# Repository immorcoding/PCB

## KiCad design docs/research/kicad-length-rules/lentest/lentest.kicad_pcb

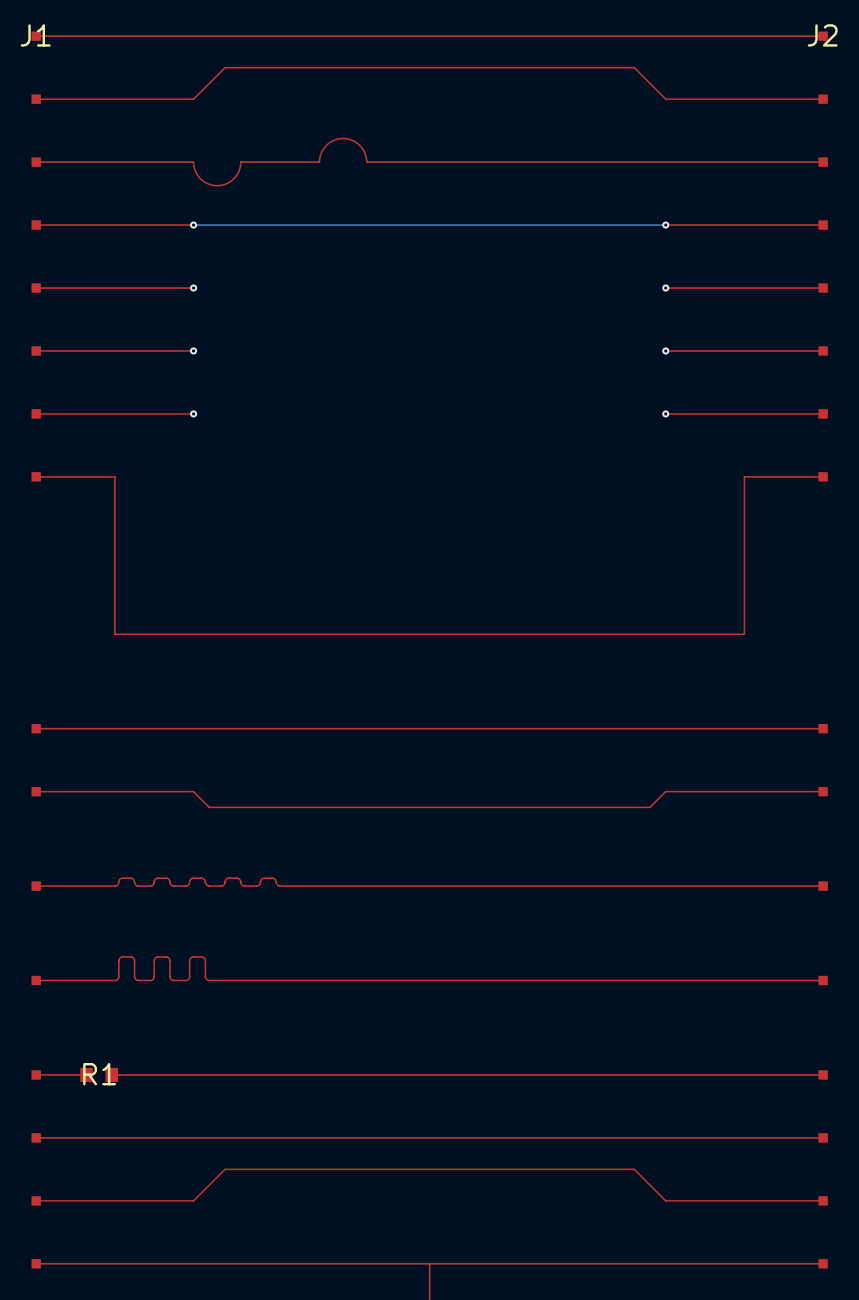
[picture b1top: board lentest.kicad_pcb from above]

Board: 6 copper layers, 3 parts (0 on the bottom side), 17 nets.

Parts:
J1: J1
J2: J2
R1: R1

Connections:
/CLK2_A: J1.13, R1.1
/CLK2_B: J2.13, R1.2
/QSPI_CLK: J1.14, J2.14
/QSPI_IO0: J1.15, J2.15
/SDCLK: J1.10, J2.10
/SDRAM_D0: J1.1, J2.1
/SDRAM_D1: J1.2, J2.2
/SDRAM_D2: J1.3, J2.3
/SDRAM_D3: J1.4, J2.4
/SDRAM_D4: J1.5, J2.5
/SDRAM_D5: J1.6, J2.6
/SDRAM_D6: J1.7, J2.7
/SDRAM_D7: J1.8, J2.8
/SDRAM_D8: J1.9, J2.9
/SDRAM_D9: J1.11, J2.11
/SDRAM_D10: J1.12, J2.12
/TBR: J1.16, J2.16

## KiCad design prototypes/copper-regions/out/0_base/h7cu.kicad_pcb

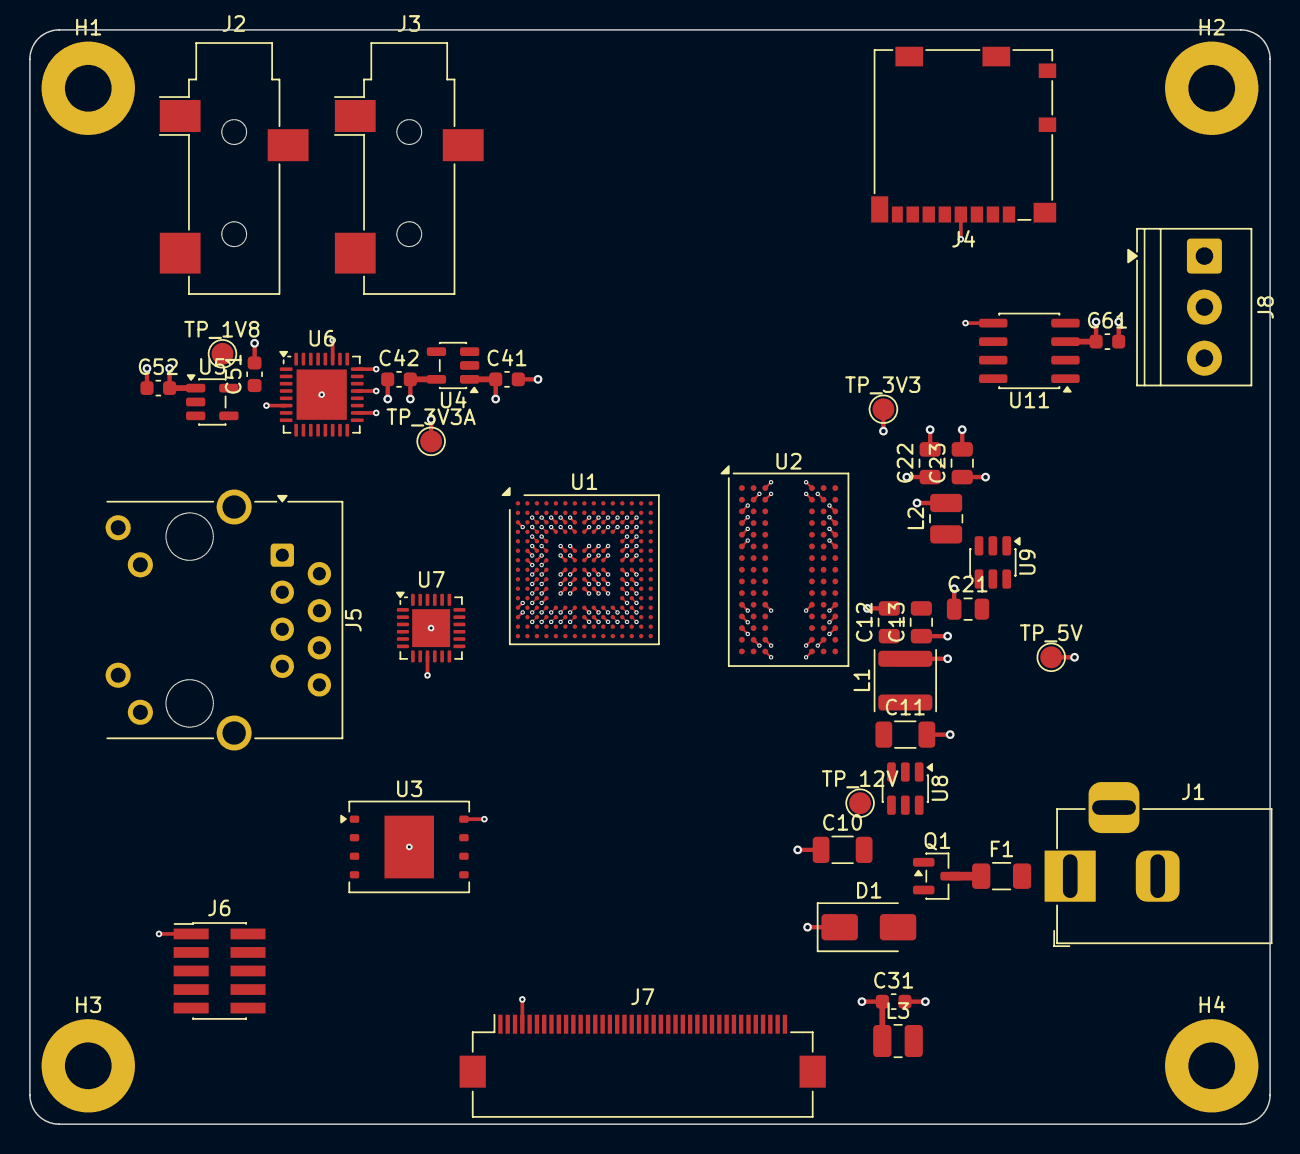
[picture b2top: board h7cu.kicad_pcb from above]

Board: 6 copper layers, 85.0 x 75.0 mm, 46 parts (0 on the bottom side), 14 nets.

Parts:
C10, C11: C_1206_3216Metric
C12, C13, C21, C22, C23: C_0805_2012Metric
C31, C41, C42, C51, C52, C61: C_0603_1608Metric
D1: TVS; D_SMA
F1: Fuse_1206_3216Metr; Fuse_1206_3216Metric
H1, H2, H3, H4: MountingHole_3.2mm; MountingHole_3.2mm_M3_Pad
J1: BarrelJack_Horizon; BarrelJack_Horizontal
J2, J3: Jack_3.5mm_CUI_SJ-; Jack_3.5mm_CUI_SJ-3523-SMT_Horizontal
J4: microSD_HC_Molex_1; microSD_HC_Molex_104031-0811
J5: RJ45_Wuerth_749901; RJ45_Wuerth_7499010211A_Horizontal
J6: PinHeader_2x05_P1.; PinHeader_2x05_P1.27mm_Vertical_SMD
J7: Hirose_FH12-40S-0.; Hirose_FH12-40S-0.5SH_1x40-1MP_P0.50mm_Horizontal
J8: TerminalBlock_Phoe; TerminalBlock_Phoenix_PT-1,5-3-3.5-H_1x03_P3.50mm_Horizontal
L1: L_Changjiang_FNR40; L_Changjiang_FNR4020S
L2, L3: L_1008_2520Metric
Q1: P-MOS; SOT-23
TP_1V8, TP_3V3, TP_3V3A, TP_5V, TP_12V: TestPoint_Pad_D1.5; TestPoint_Pad_D1.5mm
U1: STM32H743IIK6; UFBGA-201_10x10mm_Layout15x15_P0.65mm
U2: IS42S32800J; BGA-90_8.0x13.0mm_Layout2x3x15_P0.8mm
U3: W25Q128JV; WSON-8-1EP_8x6mm_P1.27mm_EP3.4x4.3mm
U4: TPS7A2033; SOT-23-5
U5: TPS7A2018; SOT-23-5
U6: TLV320AIC3104; QFN-32-1EP_5x5mm_P0.5mm_EP3.45x3.45mm
U7: LAN8742A; QFN-24-1EP_4x4mm_P0.5mm_EP2.6x2.6mm
U8: LMR51420; SOT-23-6
U9: TPS62A02; SOT-23-6
U11: TCAN1042HGV; SOIC-8_3.9x4.9mm_P1.27mm

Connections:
+1V8: C51.1, TP_1V8.1, U5.5, U6.4
+3V3: C22.1, C23.1, C52.2, J4.4, J6.1, J7.4, L2.2, TP_3V3.1, U1.C1, U1.C5, U1.C6, U1.C7, U1.C8, U1.C9, U1.F3, U1.G3, U1.G13, U1.H13, U1.J12, U1.J13, U1.K4, U1.N8, U1.N9, U1.N10, U2.A7, U2.B2, U2.B7, U2.C9, U2.D9, U2.E1, U2.F9, U2.L1, U2.L7, U2.M9, U2.N9, U2.P2, U2.P7, U2.R7, U3.8, U5.1, U6.6, U7.9, U11.5
+3V3A: C42.2, TP_3V3A.1, U4.5, U6.18, U6.21, U6.24, U6.27
+5V: C12.1, C13.1, C21.2, C31.1, C41.1, C61.1, L1.2, L3.1, TP_5V.1, U4.1, U9.4, U11.3
+12V: C10.2, C11.1, D1.2, Q1.2, TP_12V.1, U8.3
+12V_F: F1.1, Q1.3
+12V_IN: F1.2, J1.1
CANH: J8.1, U11.7
CANL: J8.2, U11.6
GND: C10.1, C11.2, C12.2, C13.2, C21.1, C22.2, C23.2, C31.2, C41.2, C42.1, C51.2, C52.1, C61.2, D1.1, H1.1, H2.1, H3.1, H4.1, J1.2, J1.3, J2.S, J3.S, J4.6, J4.SH, J5.8, J5.SH, J6.3, J6.5, J6.9, J7.3, J7.29, J7.36, J7.MP, J8.3, U1.D5, U1.D7, U1.D8, U1.D9, U1.F2, U1.F6, U1.F7, U1.F8, U1.F9, U1.F10, U1.F12, U1.G2, U1.G6, U1.G7, U1.G8, U1.G9, U1.G10, U1.G12, U1.H6, U1.H7, U1.H8, U1.H9, U1.H10, U1.H12, U1.J6, U1.J7, U1.J8, U1.J9, U1.J10, U1.K6, U1.K7, U1.K8, U1.K9, U1.K10, U1.L4, U1.M1, U1.M8, U1.M9, U1.N1, U2.A3, U2.B3, U2.B8, U2.C1, U2.D1, U2.E9, U2.F1, U2.L3, U2.L9, U2.M1, U2.N1, U2.P3, U2.P8, U2.R3, U3.4, U3.9, U4.2, U5.2, U6.5, U6.19, U6.22, U6.28, U6.33, U7.25, U8.1, U9.2, U11.2
SW_3V3: L2.1, U9.3
SW_5V: L1.1, U8.2
VDDA_MCU: U1.P1, U1.R1
VDDA_PHY: J5.4, J5.5, U7.1, U7.19
